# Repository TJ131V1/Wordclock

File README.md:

## 💡 Project Description

**This repository contains all the files for my custom word clock project, inspired by QLOCKTWO EARTH 45.**
The clock is a fully functional, physical word-based timepiece built from scratch and controlled by an Arduino Nano. It includes four hidden capacitive touch sensors. In addition to telling the time, it features:

- Snake game

- Tetris game

- LED visual effects including custom scrolling text, Conway’s Game of Life, Matrix rain, and a random letter decay animation

The repository includes:

- **Arduino Code** – All source code for the microcontroller

- **KiCAD Files** – Complete circuit schematic and PCB layout

- **2D Cutting Files** – Laser-cut design files for the structural components

- **Technical Report** – In-depth 10-page report detailing the project design, implementation, and build process

## 📽️ Showcase Video (Click Thumbnail to View)

## 📸 Product Pictures

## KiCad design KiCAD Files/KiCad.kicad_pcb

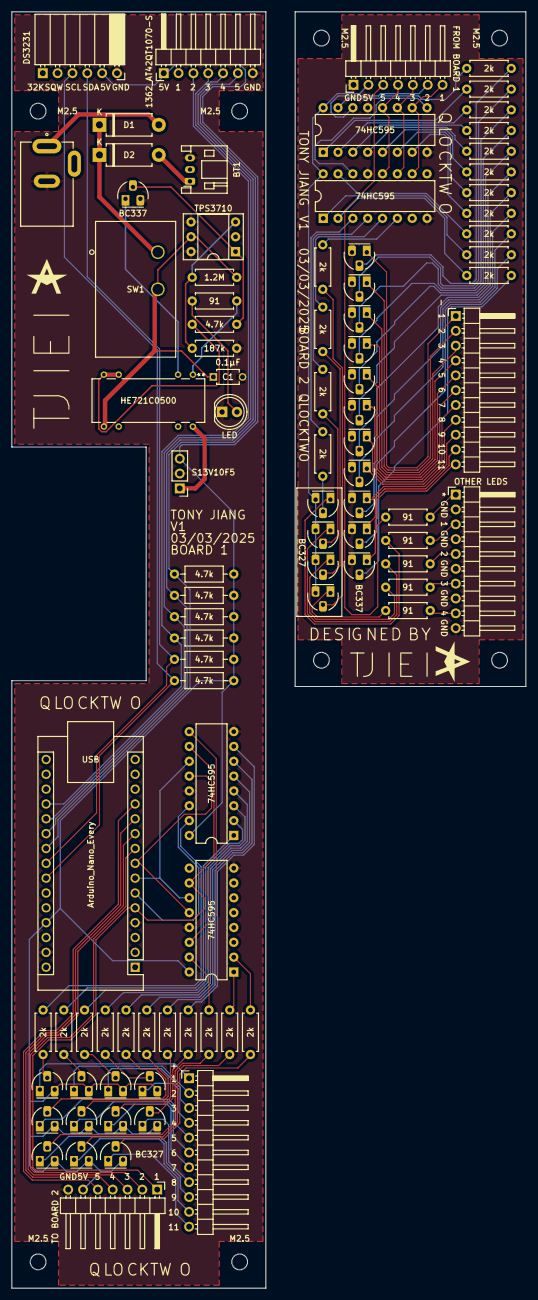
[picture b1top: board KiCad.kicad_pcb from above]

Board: 2 copper layers, 88.0 x 218.5 mm, 96 parts (0 on the bottom side), 112 nets.

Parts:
A1: Arduino_Nano_Every; Arduino_Nano
BT1: 6V; JST_PH_S3B-PH-K_1x03_P2.00mm_Horizontal
C1: 0.1µF; C_K104K10X7RF5UH5_VIS
D1, D2: D; D_DO-15_P10.16mm_Horizontal
D3: LED; LED_D5.0mm
J1, J2: Screw_Terminal_01x11; PinHeader_1x11_P2.54mm_Horizontal
J3: Barrel_Jack_Switch 10V; BarrelJack_CUI_PJ-002B_Horizontal
J4: Screw_Terminal_01x10; PinHeader_1x10_P2.54mm_Horizontal
M2.5, M2.5#2, M2.5#3, M2.5#4, M2.5#5, M2.5#6, M2.5#7, M2.5#8: MountingHole_2.7mm_M2.5
Q1, Q2, Q3, Q4, Q5, Q6, Q7, Q8, Q9, Q10, Q11, Q17, Q19, Q21, Q23: BC327; TO-92_Inline_Medium
Q12, Q13, Q14, Q15, Q16, Q18, Q20, Q22, Q24, Q25, Q26, Q27: BC337; TO-92_Inline_Medium
R1, R2, R3, R4, R5, R6, R7, R8, R9, R10, R11, R29, R30, R31, R33, R36, R37, R39, R41, R43, R46, R48, R49, R50, R51, R52: 2k; R_Axial_DIN0207_L6.3mm_D2.5mm_P7.62mm_Horizontal
R12, R13, R14, R15, R16, R17: 4.7k; R_Axial_DIN0207_L6.3mm_D2.5mm_P10.16mm_Horizontal
R32: 1.2M; R_Axial_DIN0207_L6.3mm_D2.5mm_P7.62mm_Horizontal
R34, R40, R42, R44, R45, R47: 91; R_Axial_DIN0207_L6.3mm_D2.5mm_P7.62mm_Horizontal
R35: 4.7k; R_Axial_DIN0207_L6.3mm_D2.5mm_P7.62mm_Horizontal
R38: 187k; R_Axial_DIN0207_L6.3mm_D2.5mm_P7.62mm_Horizontal
SW1: SW_SPST; SW_SPST_S101031MS02Q_CNK
U1, U2, U6, U9: 74HC595; DIP-16_W7.62mm
U3: 1362_AT42QT1070-S; PinHeader_1x07_P2.54mm_Horizontal
U4: DS3231; PinSocket_1x06_P2.54mm_Horizontal
U5: S13V10F5; PinHeader_1x03_P2.54mm_Vertical
U7: HE721C0500; Relay_SPDT_HE700_LTF
U8: TPS3710; DIP-6_W7.62mm_Socket

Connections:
+5V: A1.27 (+5V), Q1.3 (E), Q2.3 (E), Q3.3 (E), Q4.3 (E), Q5.3 (E), Q6.3 (E), Q7.3 (E), Q8.3 (E), Q9.3 (E), Q10.3 (E), Q11.3 (E), Q17.3 (E), Q19.3 (E), Q21.3 (E), Q23.3 (E), R12.1, R13.1, R14.1, R15.1, R16.1, R17.1, U1.16 (VCC), U2.16 (VCC), U3.1 (VDD), U4.5 (VCC), U5.3 (VOUT), U6.16 (VCC), U9.16 (VCC)
/LED Matrix/5V1: J1.1, Q1.1 (C)
/LED Matrix/5V2: J1.2, Q2.1 (C)
/LED Matrix/5V3: J1.3, Q3.1 (C)
/LED Matrix/5V4: J1.4, Q4.1 (C)
/LED Matrix/5V5: J1.5, Q5.1 (C)
/LED Matrix/5V6: J1.6, Q6.1 (C)
/LED Matrix/5V7: J1.7, Q7.1 (C)
/LED Matrix/5V8: J1.8, Q8.1 (C)
/LED Matrix/5V9: J1.9, Q9.1 (C)
/LED Matrix/5V10: J1.10, Q10.1 (C)
/LED Matrix/5V11: J1.11, Q11.1 (C)
/LED Matrix/GND1: J2.1, Q12.1 (C)
/LED Matrix/GND2: J2.2, Q13.1 (C)
/LED Matrix/GND3: J2.3, Q14.1 (C)
/LED Matrix/GND4: J2.4, Q15.1 (C)
/LED Matrix/GND5: J2.5, Q16.1 (C)
/LED Matrix/GND6: J2.6, Q18.1 (C)
/LED Matrix/GND7: J2.7, Q20.1 (C)
/LED Matrix/GND8: J2.8, Q22.1 (C)
/LED Matrix/GND9: J2.9, Q24.1 (C)
/LED Matrix/GND10: J2.10, Q25.1 (C)
/LED Matrix/GND11: J2.11, Q26.1 (C)
GND: A1.4 (GND), A1.29 (GND), BT1.3 (-), C1.2, D3.1 (K), J3.2, J4.2, J4.4, J4.6, J4.8, J4.10, Q12.3 (E), Q13.3 (E), Q14.3 (E), Q15.3 (E), Q16.3 (E), Q18.3 (E), Q20.3 (E), Q22.3 (E), Q24.3 (E), Q25.3 (E), Q26.3 (E), Q27.3 (E), R38.2, U1.8 (GND), U1.13 (~OE), U2.8 (GND), U2.13 (~OE), U3.7 (GND), U4.6 (GND), U5.2 (GND), U6.8 (GND), U6.13 (~OE), U8.2 (GND), U8.4 (GND), U8.6 (GND), U9.8 (GND), U9.13 (~OE)
unnamed: A1.19 (A0), R12.2, U3.3 (OUT2)
unnamed: A1.20 (A1), R13.2, U3.4 (OUT3)
unnamed: A1.21 (A2), R14.2, U3.5 (OUT4)
unnamed: A1.22 (A3), R15.2, U3.6 (OUT5)
unnamed: A1.5 (D2), U1.10 (~SRCLR), U2.10 (~SRCLR), U6.10 (~SRCLR), U9.10 (~SRCLR)
unnamed: A1.6 (D3), U1.14 (SER)
unnamed: A1.7 (D4), U1.11 (SRCLK), U2.11 (SRCLK)
unnamed: A1.8 (D5), U1.12 (RCLK), U2.12 (RCLK)
unnamed: A1.9 (D6), U6.14 (SER)
unnamed: A1.10 (D7), U6.11 (SRCLK), U9.11 (SRCLK)
unnamed: A1.11 (D8), U6.12 (RCLK), U9.12 (RCLK)
unnamed: A1.12 (D9), R40.2
unnamed: A1.24 (SCL/A5), R17.2, U4.3 (SCL)
unnamed: A1.23 (SDA/A4), R16.2, U4.4 (SDA)
unnamed: BT1.1 (+), D2.2 (A)
unnamed: D1.2 (A), J3.1
unnamed: D1.1 (K), D2.1 (K), SW1.1 (A)
unnamed: D3.2 (A), R34.2
unnamed: J4.1, R40.1
unnamed: J4.3, R42.1
unnamed: J4.5, R44.1
unnamed: J4.7, R45.1
unnamed: J4.9, R47.1
unnamed: Q1.2 (B), R1.2
unnamed: Q2.2 (B), R2.2
unnamed: Q3.2 (B), R3.2
unnamed: Q4.2 (B), R4.2
unnamed: Q5.2 (B), R5.2
unnamed: Q6.2 (B), R6.2
unnamed: Q7.2 (B), R7.2
unnamed: Q8.2 (B), R8.2
unnamed: Q9.2 (B), R9.2
unnamed: Q10.2 (B), R10.2
unnamed: Q11.2 (B), R11.2
unnamed: Q12.2 (B), R29.2
unnamed: Q13.2 (B), R30.2
unnamed: Q14.2 (B), R31.2
unnamed: Q15.2 (B), R33.2
unnamed: Q16.2 (B), R36.2
unnamed: Q17.2 (B), R48.1
unnamed: Q17.1 (C), R42.2
unnamed: Q18.2 (B), R37.2
unnamed: Q19.2 (B), R49.1
unnamed: Q19.1 (C), R44.2
unnamed: Q20.2 (B), R39.2
unnamed: Q21.2 (B), R51.1
unnamed: Q21.1 (C), R45.2
unnamed: Q22.2 (B), R41.2
unnamed: Q23.2 (B), R52.1
unnamed: Q23.1 (C), R47.2
unnamed: Q24.2 (B), R43.2
unnamed: Q25.2 (B), R46.2
unnamed: Q26.2 (B), R50.2
unnamed: Q27.2 (B), R35.2, U8.1 (OUT)
unnamed: Q27.1 (C), U7.2
unnamed: R34.1, U7.1
unnamed: R35.1, U7.6, U7.7
unnamed: C1.1, R32.1, SW1.2 (B), U7.8, U8.5 (VDD)
unnamed: R1.1, U1.15 (QA)
unnamed: R2.1, U1.1 (QB)
unnamed: R3.1, U1.2 (QC)
unnamed: R4.1, U1.3 (QD)
unnamed: R5.1, U1.4 (QE)
unnamed: R6.1, U1.5 (QF)
unnamed: R7.1, U1.6 (QG)
unnamed: U1.9 (QH'), U2.14 (SER)
unnamed: R8.1, U1.7 (QH)
unnamed: R9.1, U2.15 (QA)
unnamed: R10.1, U2.1 (QB)
unnamed: R11.1, U2.2 (QC)
unnamed: U5.1 (VIN), U7.14
unnamed: R29.1, U6.15 (QA)
unnamed: R30.1, U6.1 (QB)
unnamed: R31.1, U6.2 (QC)
unnamed: R33.1, U6.3 (QD)
unnamed: R36.1, U6.4 (QE)
unnamed: R37.1, U6.5 (QF)
unnamed: R39.1, U6.6 (QG)
unnamed: U6.9 (QH'), U9.14 (SER)
unnamed: R41.1, U6.7 (QH)
unnamed: R32.2, R38.1, U8.3 (SENSE)
unnamed: R43.1, U9.15 (QA)
unnamed: R46.1, U9.1 (QB)
unnamed: R50.1, U9.2 (QC)
unnamed: R48.2, U9.3 (QD)
unnamed: R49.2, U9.4 (QE)
unnamed: R51.2, U9.5 (QF)
unnamed: R52.2, U9.6 (QG)

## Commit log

2025-07-02 Create test
2025-07-02 Create placeholder
2025-07-02 Made some changes.
2025-07-10 Made some Changes
